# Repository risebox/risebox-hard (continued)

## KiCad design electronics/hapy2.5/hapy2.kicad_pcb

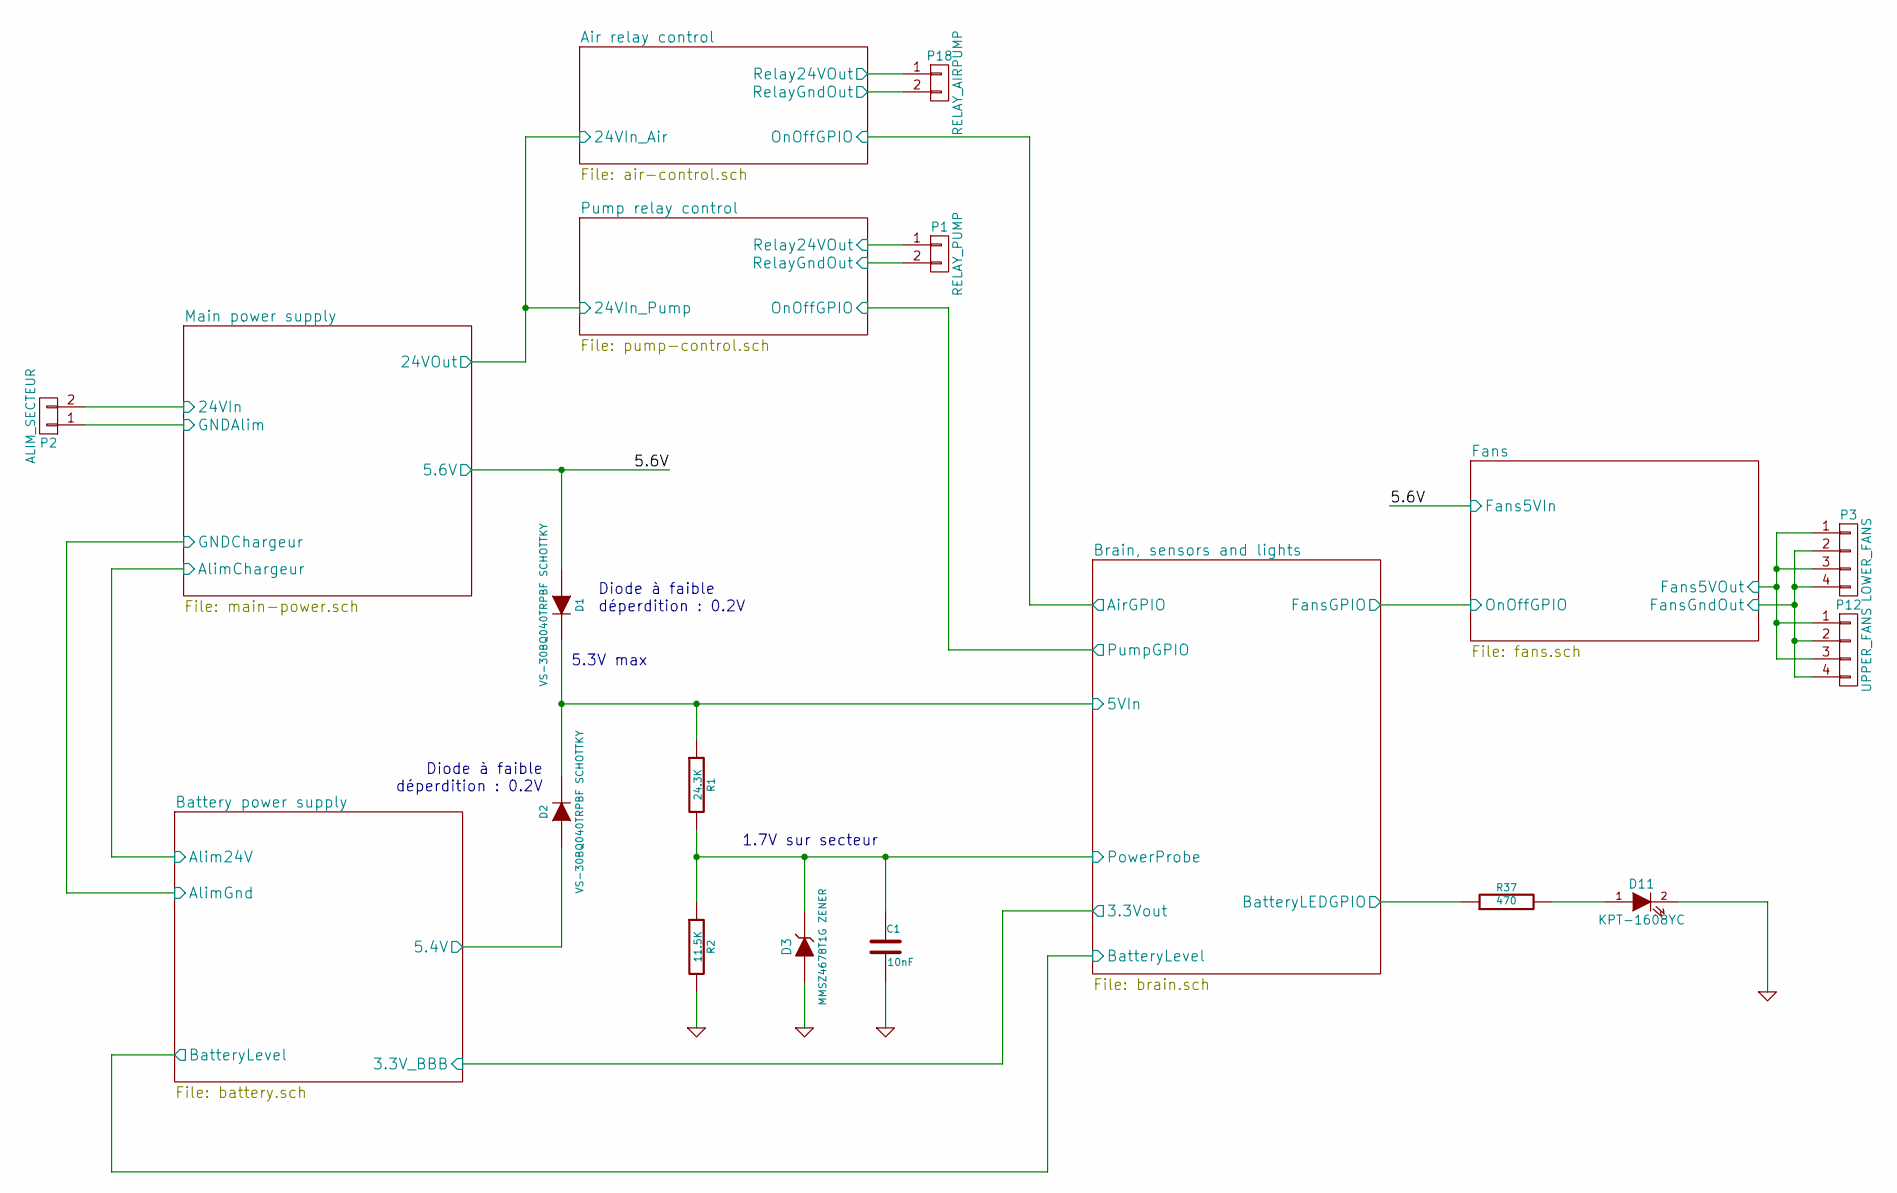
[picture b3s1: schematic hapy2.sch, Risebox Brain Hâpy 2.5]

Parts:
C1: 10nF; C_0402
D1, D2: VS-30BQ040TRPBF SCHOTTKY; DO-214AB
D3: MMSZ4678T1G ZENER; DIODE_SOD-123
D11: KPT-1608YC; LED_KPH_1608
P1: RELAY_PUMP; mpt_0,5%2f2-2,54
P2: ALIM_SECTEUR; mpt_0,5%2f2-2,54
P3: LOWER_FANS; mpt_0,5%2f4-2,54
P12: UPPER_FANS; mpt_0,5%2f4-2,54
P18: RELAY_AIRPUMP; mpt_0,5%2f2-2,54
R1: 24.3K; R_0603
R2: 11.5K; R_0603
R37: 470; R_0603

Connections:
/Air relay control/24VIn_Air: P1.1, P18.1; also elsewhere on the board
/Air relay control/RelayGndOut: P18.2; also elsewhere on the board
/Battery power supply/5.4V: D2.1 (A); also elsewhere on the board
/Brain, sensors and lights/5VIn: D1.2 (K), D2.2 (K), R1.1; also elsewhere on the board
/Brain, sensors and lights/BatteryLEDGPIO: R37.1; also elsewhere on the board
/Brain, sensors and lights/PowerProbe: C1.1, D3.2 (K), R1.2, R2.1; also elsewhere on the board
/Fans/FansGndOut: P3.2, P3.4, P12.2, P12.4; also elsewhere on the board
/Main power supply/5.6V: D1.1 (A), P3.1, P3.3, P12.1, P12.3; also elsewhere on the board
/Main power supply/24VIn: P2.2; also elsewhere on the board
/Pump relay control/RelayGndOut: P1.2; also elsewhere on the board
GND: C1.2, D3.1 (A), D11.2 (K), P2.1, R2.2; also elsewhere on the board
unnamed: D11.1 (A), R37.2

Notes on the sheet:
Diode à faible déperdition : 0.2V
5.3V max
1.7V sur secteur

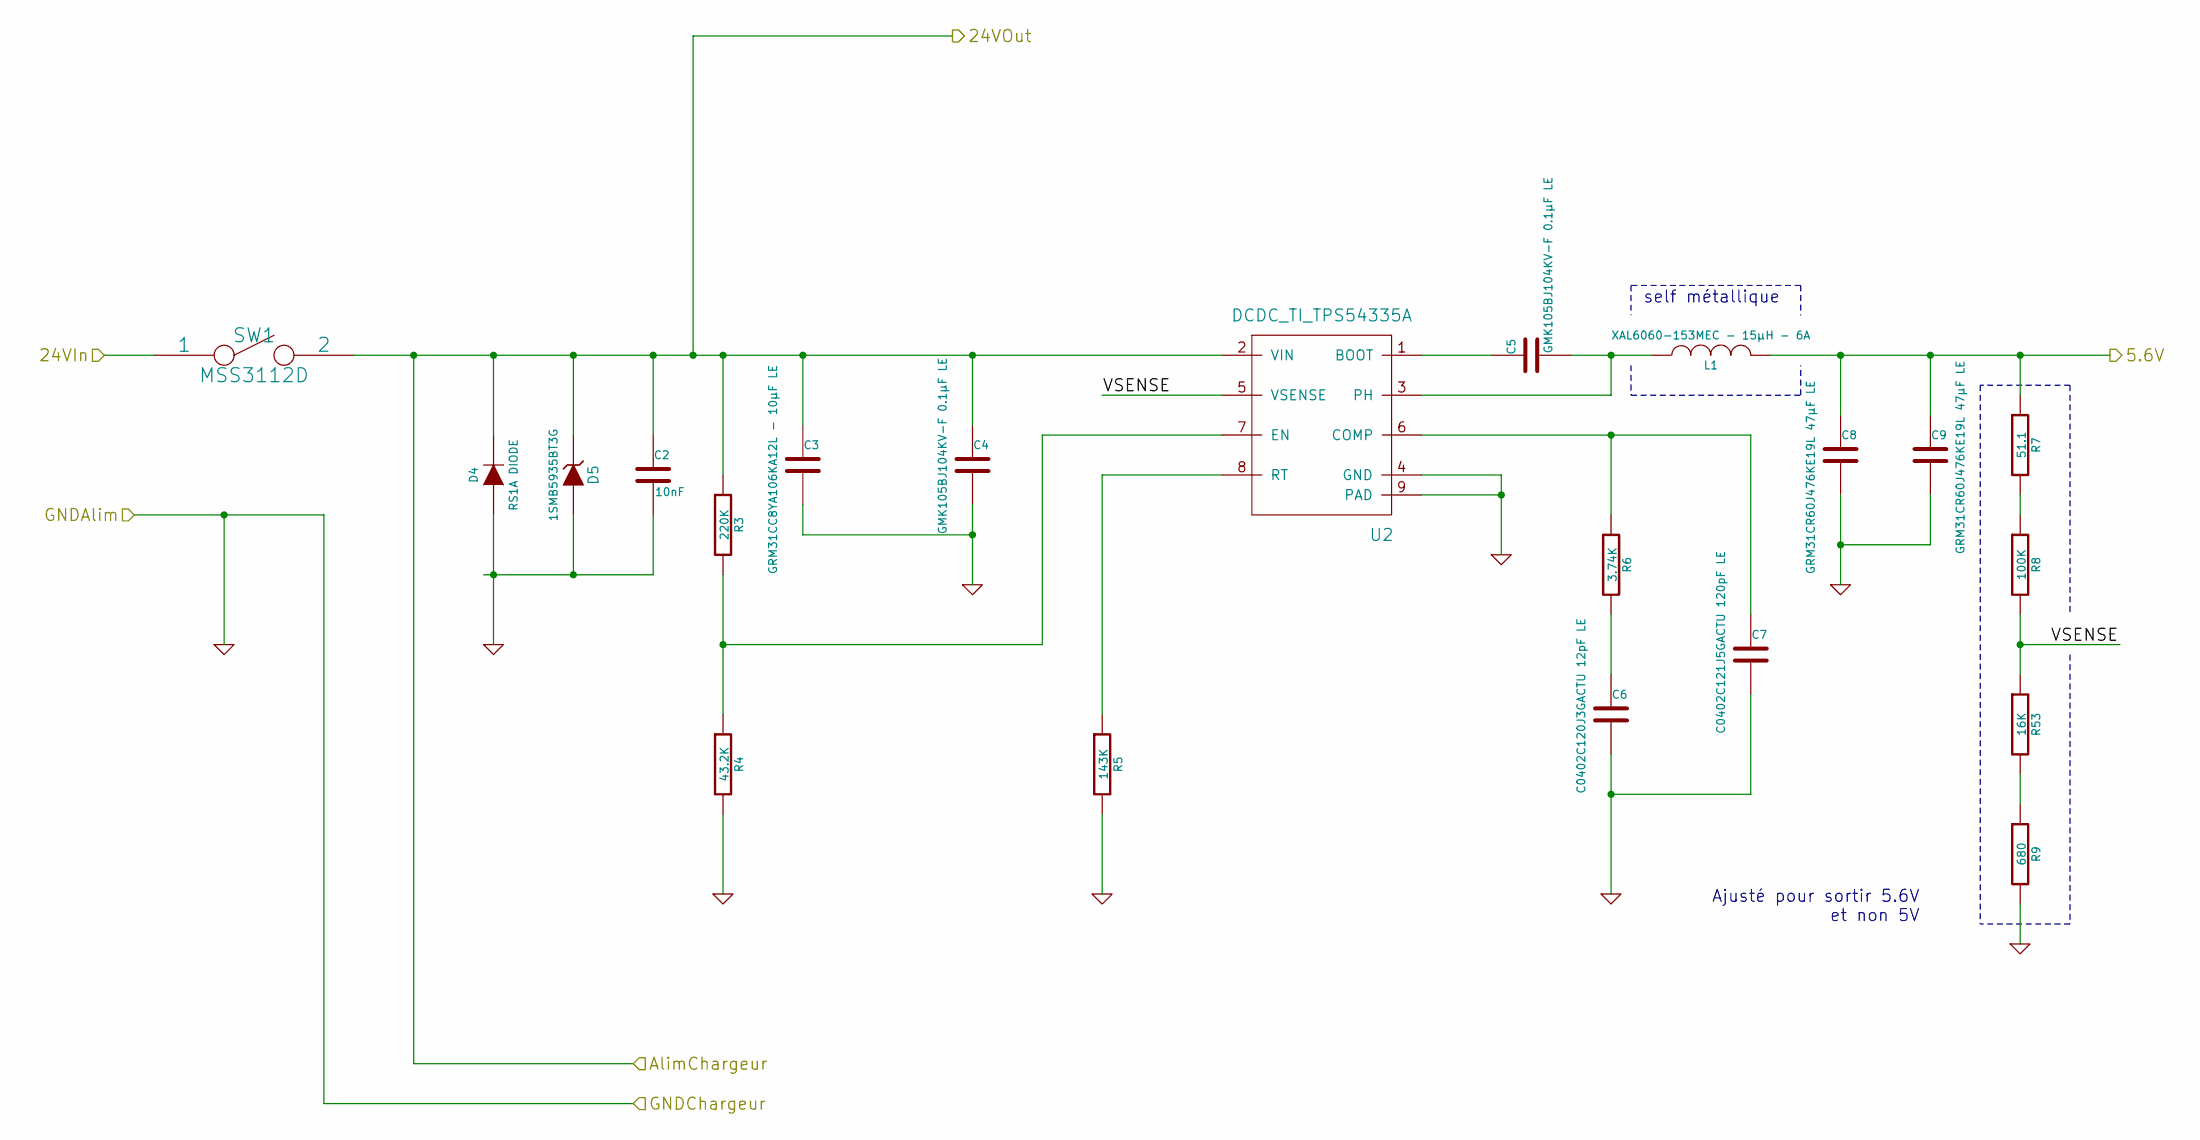
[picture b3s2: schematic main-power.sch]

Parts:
C2: 10nF; C_1206
C3: GRM31CC8YA106KA12L - 10µF LE; C_1206
C4, C5: GMK105BJ104KV-F 0.1µF LE; C_0402
C6: C0402C120J3GACTU 12pF LE; C_0402
C7: C0402C121J5GACTU 120pF LE; C_0402
C8, C9: GRM31CR60J476KE19L 47µF LE; C_1206
D4: RS1A DIODE; AB2_DO-214AC
D5: 1SMB5935BT3G; DIODE_SMB_Standard
L1: XAL6060-153MEC - 15µH - 6A; SELF_COILCRAFT_XAL6060-153
R3: 220K; R_0603
R4: 43.2K; R_0603
R5: 143K; R_0603
R6: 3.74K; R_0603
R7: 51.1; R_0603
R8: 100K; R_0603
R9: 680; R_0603
R53: 16K; R_0603
SW1: MSS3112D; SPDT_MSS3112D
U2: DCDC_TI_TPS54335A; DCDC-TPS54335A

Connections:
/Air relay control/24VIn_Air: C2.1, C3.1, C4.1, D4.2 (K), D5.2 (K), R3.1, SW1.2, U2.2 (VIN); also elsewhere on the board
/Main power supply/5.6V: C8.1, C9.1, L1.2, R7.1; also elsewhere on the board
/Main power supply/24VIn: SW1.1; also elsewhere on the board
/Main power supply/VSENSE: R8.2, R53.1, U2.5 (VSENSE)
GND: C2.2, C3.2, C4.2, C6.2, C7.2, C8.2, C9.2, D4.1 (A), D5.1 (A), R4.2, R5.2, R9.2, U2.4 (GND), U2.9 (PAD); also elsewhere on the board
unnamed: C5.1, U2.1 (BOOT)
unnamed: C5.2, L1.1, U2.3 (PH)
unnamed: C6.1, R6.2
unnamed: C7.1, R6.1, U2.6 (COMP)
unnamed: R3.2, R4.1, U2.7 (EN)
unnamed: R5.1, U2.8 (RT)
unnamed: R7.2, R8.1
unnamed: R9.1, R53.2

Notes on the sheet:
self métallique
Ajusté pour sortir 5.6V et non 5V

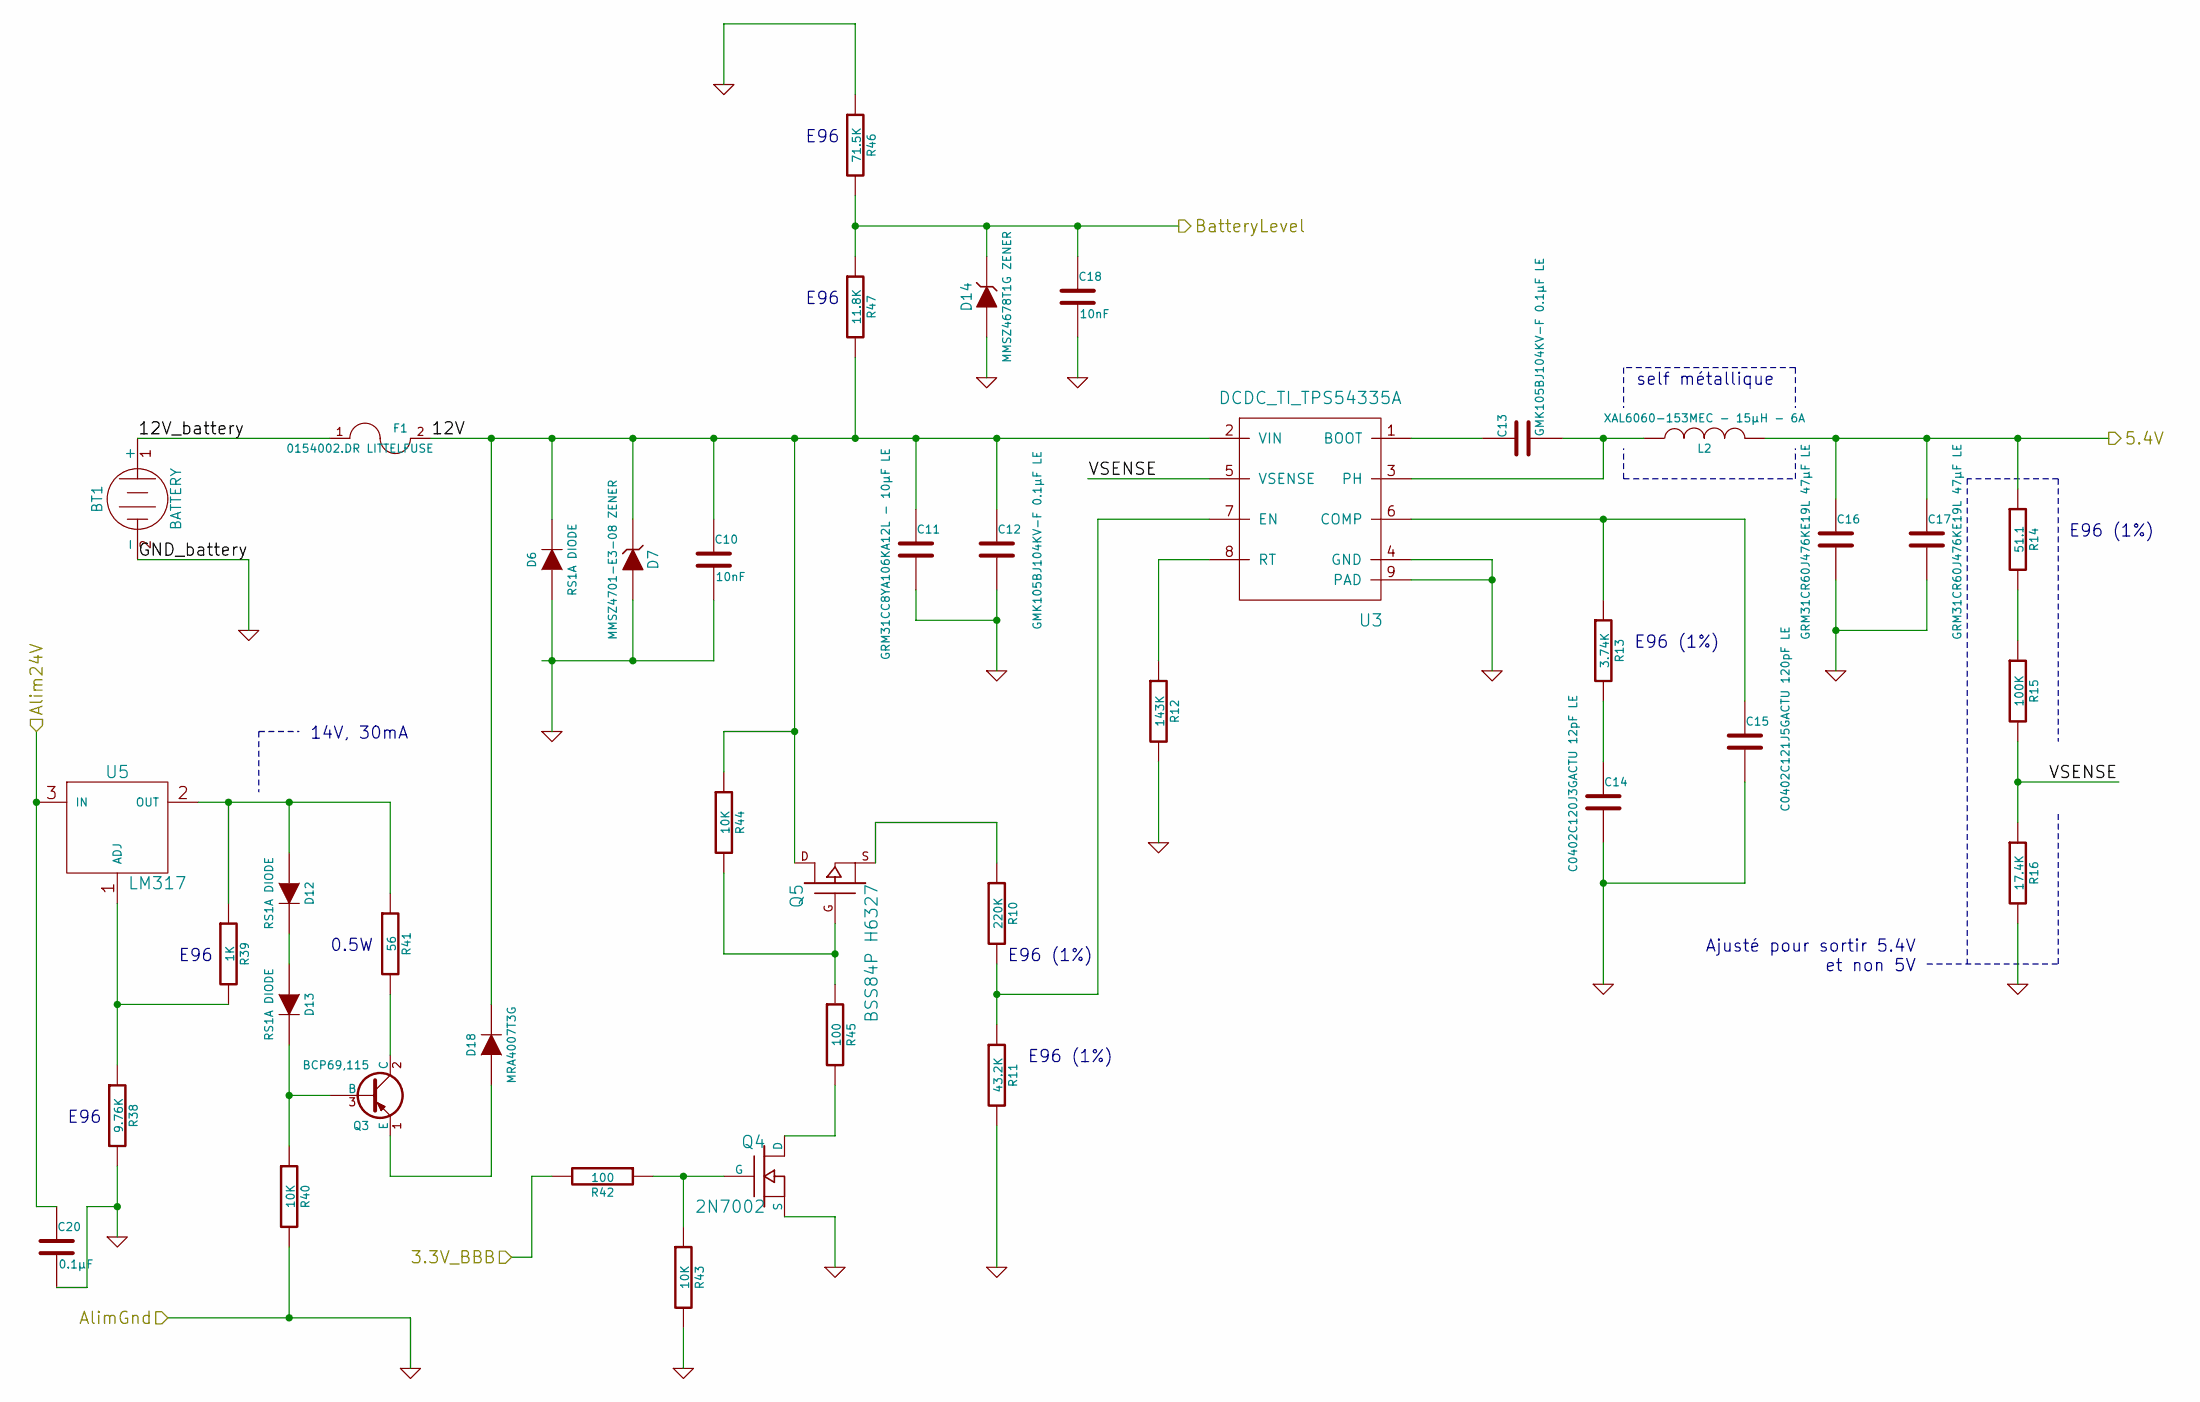
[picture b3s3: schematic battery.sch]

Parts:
BT1: BATTERY; mpt_0,5%2f2-2,54
C10: 10nF; C_1206
C11: GRM31CC8YA106KA12L - 10µF LE; C_1206
C12: GMK105BJ104KV-F 0.1µF LE; C_1206
C13: GMK105BJ104KV-F 0.1µF LE; C_0402
C14: C0402C120J3GACTU 12pF LE; C_0402
C15: C0402C121J5GACTU 120pF LE; C_0402
C16, C17: GRM31CR60J476KE19L 47µF LE; C_1206
C18: 10nF; C_0402
C20: 0.1µF
D6, D12, D13: RS1A DIODE; AB2_DO-214AC
D7: MMSZ4701-E3-08 ZENER; DIODE_SOD-123
D14: MMSZ4678T1G ZENER; DIODE_SOD-123
D18: MRA4007T3G
F1: 0154002.DR LITTELFUSE; LITTELFUSE_0154002.DR
L2: XAL6060-153MEC - 15µH - 6A; SELF_COILCRAFT_XAL6060-153
Q3: BCP69,115; SOT126_SOT32_Housing_Vertical
Q4: 2N7002; SOT-23-FET
Q5: BSS84P H6327; SOT-23-FET
R10: 220K; R_0805
R11: 43.2K; R_0603
R12: 143K; R_0603
R13: 3.74K; R_0603
R14: 51.1; R_0603
R15: 100K; R_0603
R16: 17.4K; R_0603
R38: 9.76K; R_0603
R39: 1K; R_0805
R40, R43: 10K; R_0603
R41: 56; R_1206
R42, R45: 100; R_0603
R44: 10K; R_0805
R46: 71.5K; R_0603
R47: 11.8K; R_0805
U3: DCDC_TI_TPS54335A; DCDC-TPS54335A
U5: LM317; AB2_SOT223

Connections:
/Air relay control/24VIn_Air: C20.1, U5.3 (IN); also elsewhere on the board
/Battery power supply/3.3V_BBB: R42.2; also elsewhere on the board
/Battery power supply/5.4V: C16.1, C17.1, L2.2, R14.1; also elsewhere on the board
/Battery power supply/12V: C10.1, C11.1, C12.1, D6.2 (K), D7.2 (K), D18.2 (K), F1.2, Q5.D, R44.1, R47.2, U3.2 (VIN)
/Battery power supply/12V_battery: BT1.1 (+), F1.1
/Battery power supply/BatteryLevel: C18.1, D14.2 (K), R46.2, R47.1; also elsewhere on the board
/Battery power supply/VSENSE: R15.2, R16.1, U3.5 (VSENSE)
GND: BT1.2 (-), C10.2, C11.2, C12.2, C14.2, C15.2, C16.2, C17.2, C18.2, C20.2, D6.1 (A), D7.1 (A), D14.1 (A), Q4.S, R11.2, R12.2, R16.2, R38.2, R40.2, R43.2, R46.1, U3.4 (GND), U3.9 (PAD); also elsewhere on the board
unnamed: C13.1, U3.1 (BOOT)
unnamed: C13.2, L2.1, U3.3 (PH)
unnamed: C14.1, R13.2
unnamed: C15.1, R13.1, U3.6 (COMP)
unnamed: D12.1 (A), R39.1, R41.1, U5.2 (OUT)
unnamed: D12.2 (K), D13.1 (A)
unnamed: D13.2 (K), Q3.3 (B), R40.1
unnamed: D18.1 (A), Q3.1 (E)
unnamed: Q3.2 (C), R41.2
unnamed: Q4.D, R45.2
unnamed: Q4.G, R42.1, R43.1
unnamed: Q5.G, R44.2, R45.1
unnamed: Q5.S, R10.1
unnamed: R10.2, R11.1, U3.7 (EN)
unnamed: R12.1, U3.8 (RT)
unnamed: R14.2, R15.1
unnamed: R38.1, R39.2, U5.1 (ADJ)

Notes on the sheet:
self métallique
Ajusté pour sortir 5.4V et non 5V
14V, 30mA
E96 (1%)
E96
0.5W

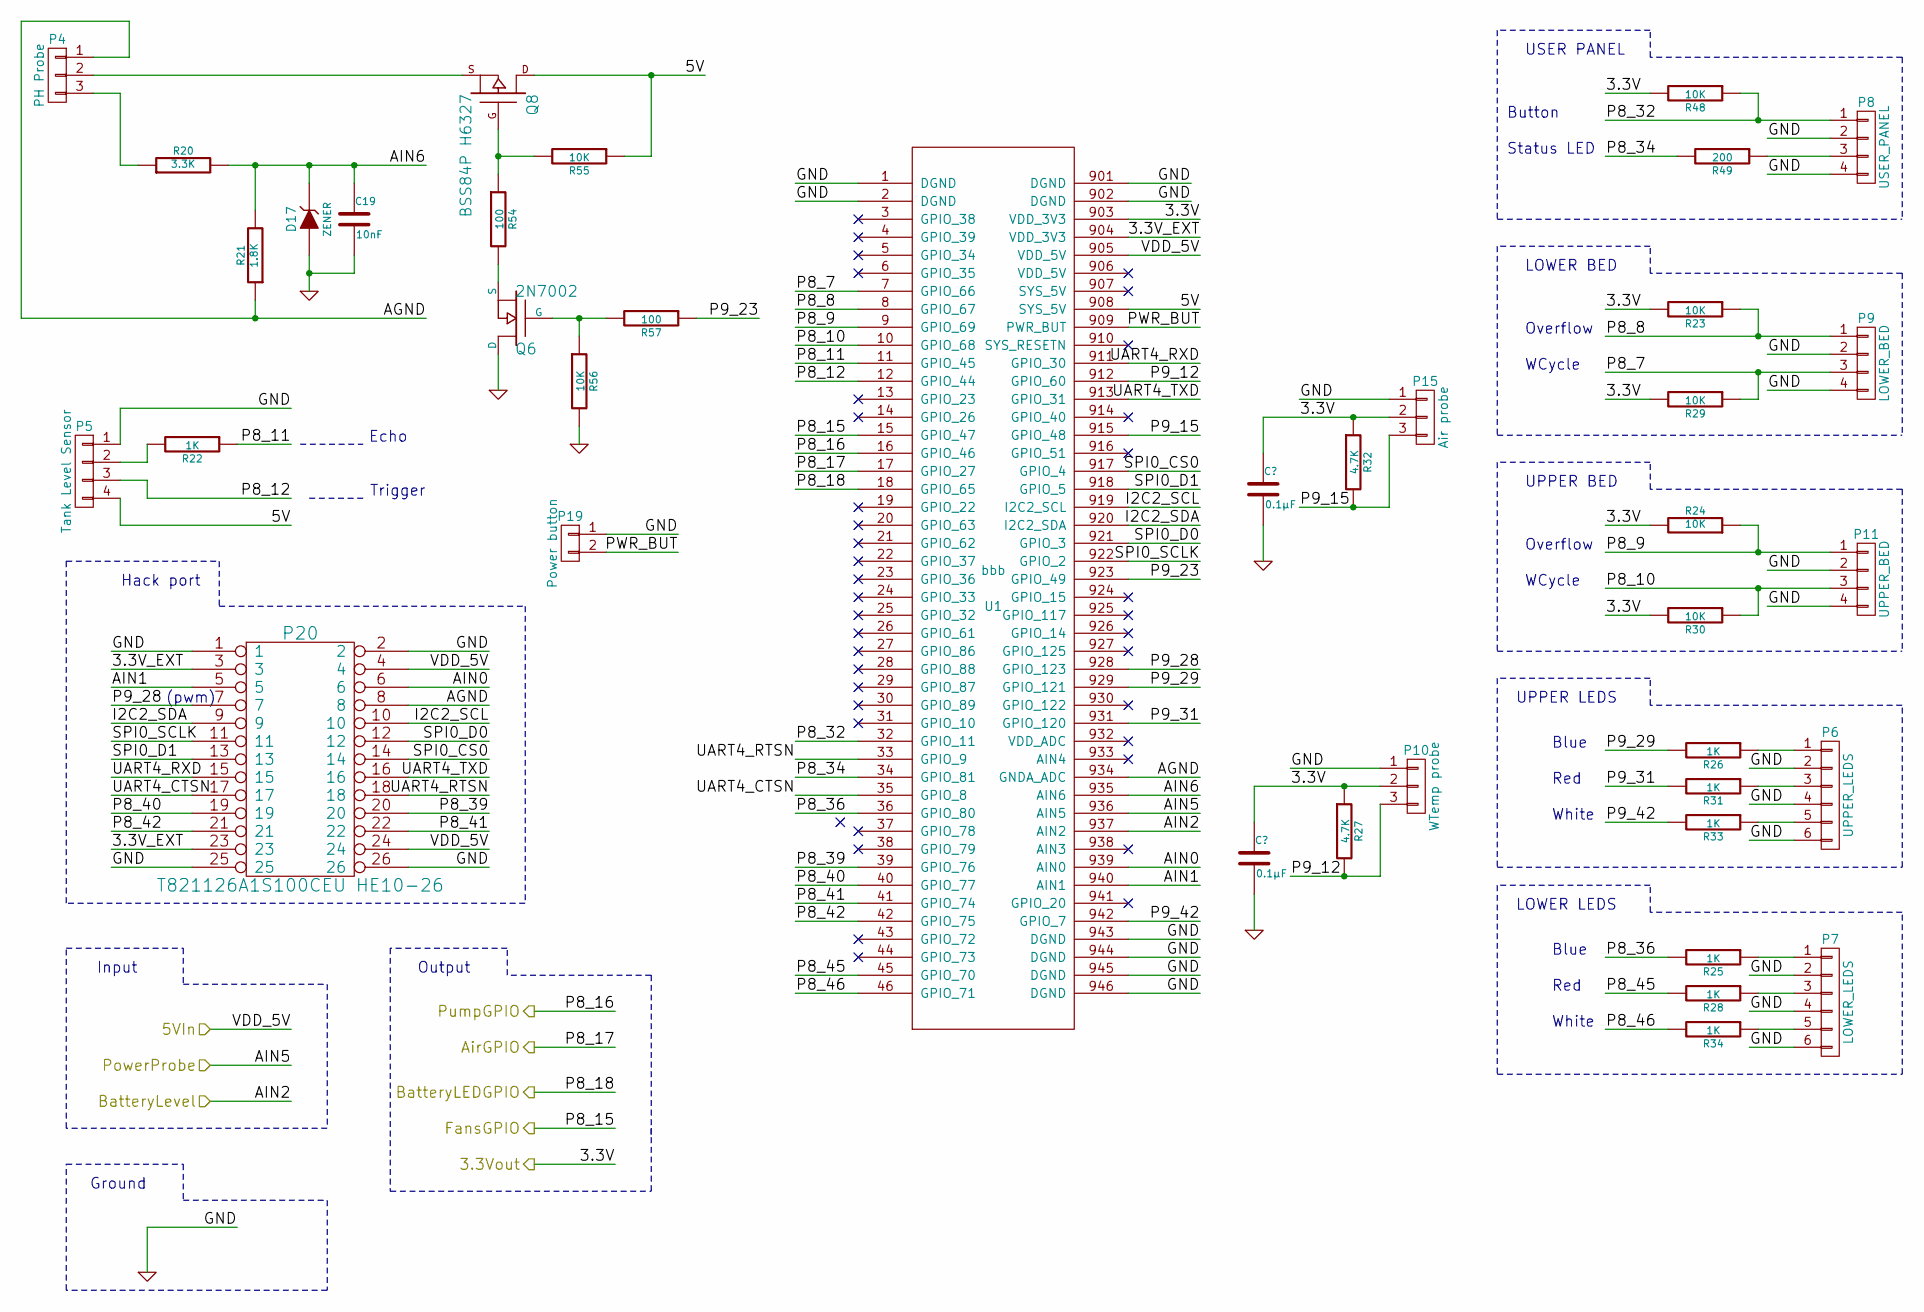
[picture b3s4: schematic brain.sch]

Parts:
C19: 10nF; C_0402
D17: ZENER; DIODE_SOD-123
P4: PH Probe; PINHEAD1-3
P5: Tank Level Sensor; mpt_0,5%2f4-2,54
P6: UPPER_LEDS; mpt_0,5%2f6-2,54
P7: LOWER_LEDS; mpt_0,5%2f6-2,54
P8: USER_PANEL; mpt_0,5%2f4-2,54
P9: LOWER_BED; mpt_0,5%2f4-2,54
P10: WTemp probe; mpt_0,5%2f3-2,54
P11: UPPER_BED; mpt_0,5%2f4-2,54
P15: Air probe; mpt_0,5%2f3-2,54
P19: Power button; mpt_0,5%2f2-2,54
P20: T821126A1S100CEU HE10-26; vasch_strip_13x2
Q6: 2N7002; SOT-23-FET
Q8: BSS84P H6327; SOT-23-FET
R20: 3.3K; R_0603
R21: 1.8K; R_0603
R22, R25, R26, R28, R31, R33, R34: 1K; R_0603
R23, R24, R29, R30, R48, R55: 10K; R_0603
R27, R32: 4.7K; R_0603
R49: 200; R_0603
R54: 100; R_0603
R56: 10K
R57: 100
U1: bbb; BBB

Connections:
/Battery power supply/3.3V_BBB: P10.2, P15.2, R23.2, R24.2, R27.1, R29.2, R30.2, R32.1, R48.2, U1.903 (VDD_3V3); also elsewhere on the board
/Battery power supply/BatteryLevel: U1.937 (AIN2); also elsewhere on the board
/Brain, sensors and lights/3.3V_EXT: P20.3, P20.23, U1.904 (VDD_3V3)
/Brain, sensors and lights/5V: P5.4, Q8.D, R55.1, U1.908 (SYS_5V)
/Brain, sensors and lights/5VIn: P20.4, P20.24, U1.905 (VDD_5V); also elsewhere on the board
/Brain, sensors and lights/AGND: P4.1, P20.8, R21.1, U1.934 (GNDA_ADC)
/Brain, sensors and lights/AIN0: P20.6, U1.939 (AIN0)
/Brain, sensors and lights/AIN1: P20.5, U1.940 (AIN1)
/Brain, sensors and lights/AIN6: C19.1, D17.2 (K), R20.2, R21.2, U1.935 (AIN6)
/Brain, sensors and lights/AirGPIO: U1.17 (GPIO_27); also elsewhere on the board
/Brain, sensors and lights/BatteryLEDGPIO: U1.18 (GPIO_65); also elsewhere on the board
/Brain, sensors and lights/FansGPIO: U1.15 (GPIO_47); also elsewhere on the board
/Brain, sensors and lights/I2C2_SCL: P20.10, U1.919 (I2C2_SCL)
/Brain, sensors and lights/I2C2_SDA: P20.9, U1.920 (I2C2_SDA)
/Brain, sensors and lights/P8_7: P9.3, R29.1, U1.7 (GPIO_66)
/Brain, sensors and lights/P8_8: P9.1, R23.1, U1.8 (GPIO_67)
/Brain, sensors and lights/P8_9: P11.1, R24.1, U1.9 (GPIO_69)
/Brain, sensors and lights/P8_10: P11.3, R30.1, U1.10 (GPIO_68)
/Brain, sensors and lights/P8_11: R22.1, U1.11 (GPIO_45)
/Brain, sensors and lights/P8_12: P5.3, U1.12 (GPIO_44)
/Brain, sensors and lights/P8_32: P8.1, R48.1, U1.32 (GPIO_11)
/Brain, sensors and lights/P8_34: R49.2, U1.34 (GPIO_81)
/Brain, sensors and lights/P8_36: R25.2, U1.36 (GPIO_80)
/Brain, sensors and lights/P8_39: P20.20, U1.39 (GPIO_76)
/Brain, sensors and lights/P8_40: P20.19, U1.40 (GPIO_77)
/Brain, sensors and lights/P8_41: P20.22, U1.41 (GPIO_74)
/Brain, sensors and lights/P8_42: P20.21, U1.42 (GPIO_75)
/Brain, sensors and lights/P8_45: R28.2, U1.45 (GPIO_70)
/Brain, sensors and lights/P8_46: R34.2, U1.46 (GPIO_71)
/Brain, sensors and lights/P9_12: P10.3, R27.2, U1.912 (GPIO_60)
/Brain, sensors and lights/P9_15: P15.3, R32.2, U1.915 (GPIO_48)
/Brain, sensors and lights/P9_23: R57.1, U1.923 (GPIO_49)
/Brain, sensors and lights/P9_28: P20.7, U1.928 (GPIO_123)
/Brain, sensors and lights/P9_29: R26.2, U1.929 (GPIO_121)
/Brain, sensors and lights/P9_31: R31.2, U1.931 (GPIO_120)
/Brain, sensors and lights/P9_42: R33.2, U1.942 (GPIO_7)
/Brain, sensors and lights/PWR_BUT: P19.2, U1.909 (PWR_BUT)
/Brain, sensors and lights/PowerProbe: U1.936 (AIN5); also elsewhere on the board
/Brain, sensors and lights/SPI0_CS0: P20.14, U1.917 (GPIO_4)
/Brain, sensors and lights/SPI0_D0: P20.12, U1.921 (GPIO_3)
/Brain, sensors and lights/SPI0_D1: P20.13, U1.918 (GPIO_5)
/Brain, sensors and lights/SPI0_SCLK: P20.11, U1.922 (GPIO_2)
/Brain, sensors and lights/UART4_CTSN: P20.17, U1.35 (GPIO_8)
/Brain, sensors and lights/UART4_RTSN: P20.18, U1.33 (GPIO_9)
/Brain, sensors and lights/UART4_RXD: P20.15, U1.911 (GPIO_30)
/Brain, sensors and lights/UART4_TXD: P20.16, U1.913 (GPIO_31)
/Pump relay control/OnOffGPIO: U1.16 (GPIO_46); also elsewhere on the board
GND: C19.2, D17.1 (A), P5.1, P6.2, P6.4, P6.6, P7.2, P7.4, P7.6, P8.2, P8.4, P9.2, P9.4, P10.1, P11.2, P11.4, P15.1, P19.1, P20.1, P20.2, P20.25, P20.26, Q6.D, R56.2, U1.1 (DGND), U1.2 (DGND), U1.901 (DGND), U1.902 (DGND), U1.943 (DGND), U1.944 (DGND), U1.945 (DGND), U1.946 (DGND); also elsewhere on the board
unnamed: P4.2, Q8.S
unnamed: P4.3, R20.1
unnamed: P5.2, R22.2
unnamed: P6.1, R26.1
unnamed: P6.3, R31.1
unnamed: P6.5, R33.1
unnamed: P7.1, R25.1
unnamed: P7.3, R28.1
unnamed: P7.5, R34.1
unnamed: P8.3, R49.1
unnamed: Q6.G, R56.1, R57.2
unnamed: Q6.S, R54.2
unnamed: Q8.G, R54.1, R55.2

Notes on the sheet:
Echo
Trigger
Input
Output
Ground
(pwm)
Hack port
Blue
Red
White
LOWER LEDS
UPPER LEDS
Overflow
WCycle
UPPER BED
LOWER BED
Button
Status LED
USER PANEL

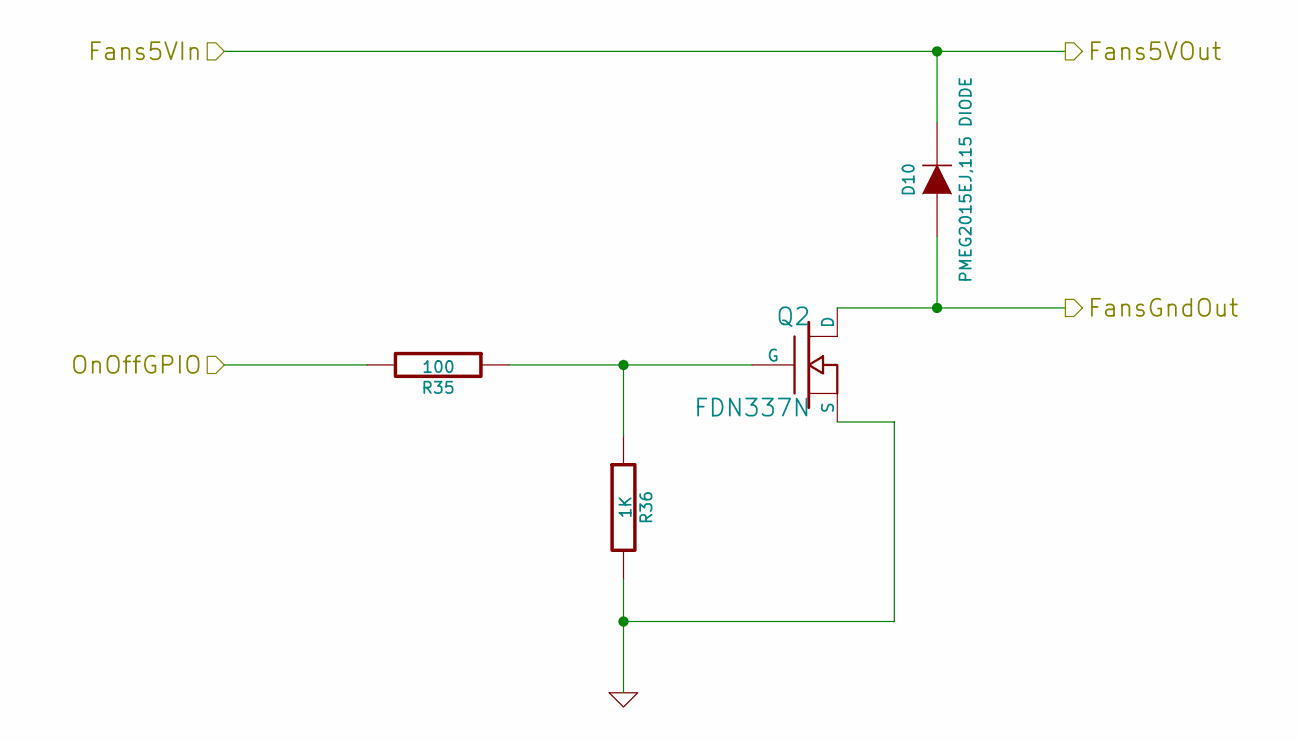
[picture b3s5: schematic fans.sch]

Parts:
D10: PMEG2015EJ,115 DIODE; DIODE_SOD-323
Q2: FDN337N; SOT-23-FET
R35: 100; R_0603
R36: 1K; R_0603

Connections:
/Brain, sensors and lights/FansGPIO: R35.2; also elsewhere on the board
/Fans/FansGndOut: D10.1 (A), Q2.D; also elsewhere on the board
/Main power supply/5.6V: D10.2 (K); also elsewhere on the board
GND: Q2.S, R36.2; also elsewhere on the board
unnamed: Q2.G, R35.1, R36.1

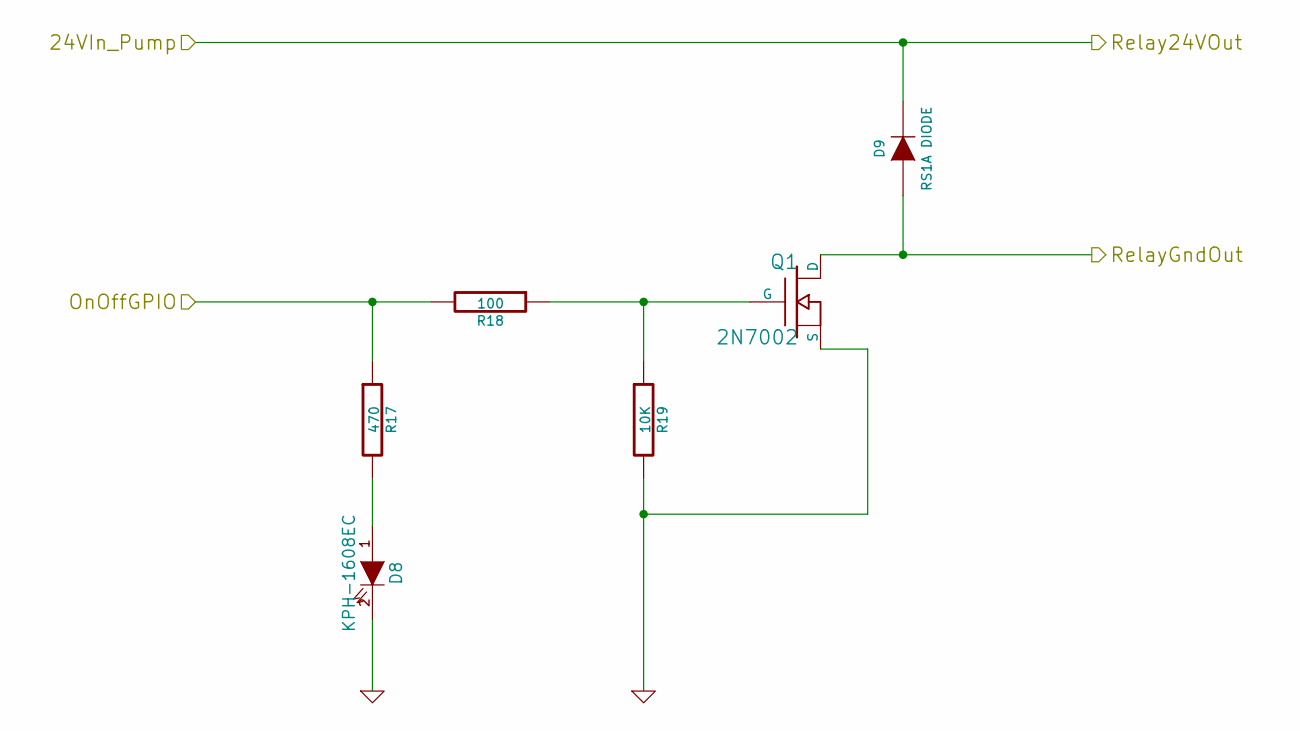
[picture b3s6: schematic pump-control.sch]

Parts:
D8: KPH-1608EC; LED_KPH_1608
D9: RS1A DIODE; AB2_DO-214AC
Q1: 2N7002; SOT-23-FET
R17: 470; R_0603
R18: 100; R_0603
R19: 10K; R_0603

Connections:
/Air relay control/24VIn_Air: D9.2 (K); also elsewhere on the board
/Pump relay control/OnOffGPIO: R17.1, R18.2; also elsewhere on the board
/Pump relay control/RelayGndOut: D9.1 (A), Q1.D; also elsewhere on the board
GND: D8.2 (K), Q1.S, R19.2; also elsewhere on the board
unnamed: D8.1 (A), R17.2
unnamed: Q1.G, R18.1, R19.1

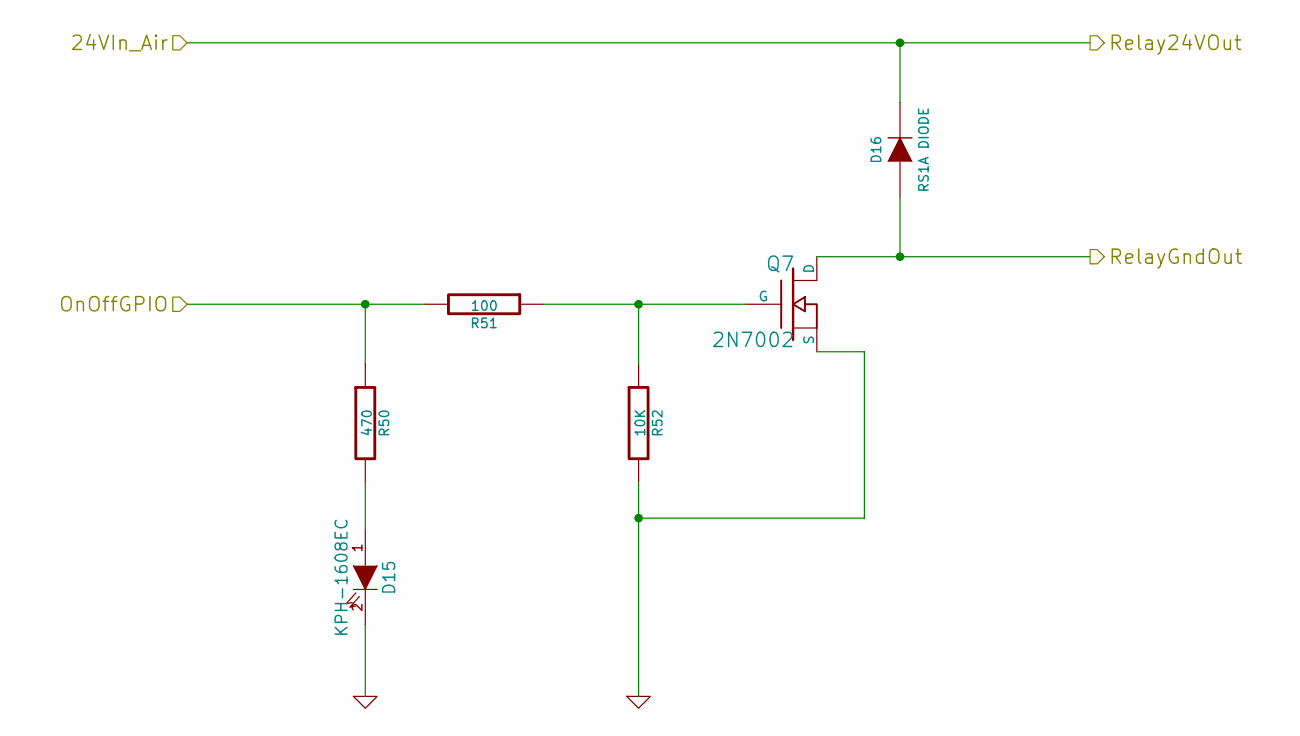
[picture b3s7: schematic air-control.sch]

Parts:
D15: KPH-1608EC; LED_KPH_1608
D16: RS1A DIODE; AB2_DO-214AC
Q7: 2N7002; SOT-23-FET
R50: 470; R_0603
R51: 100; R_0603
R52: 10K; R_0603

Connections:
/Air relay control/24VIn_Air: D16.2 (K); also elsewhere on the board
/Air relay control/RelayGndOut: D16.1 (A), Q7.D; also elsewhere on the board
/Brain, sensors and lights/AirGPIO: R50.1, R51.2; also elsewhere on the board
GND: D15.2 (K), Q7.S, R52.2; also elsewhere on the board
unnamed: D15.1 (A), R50.2
unnamed: Q7.G, R51.1, R52.1

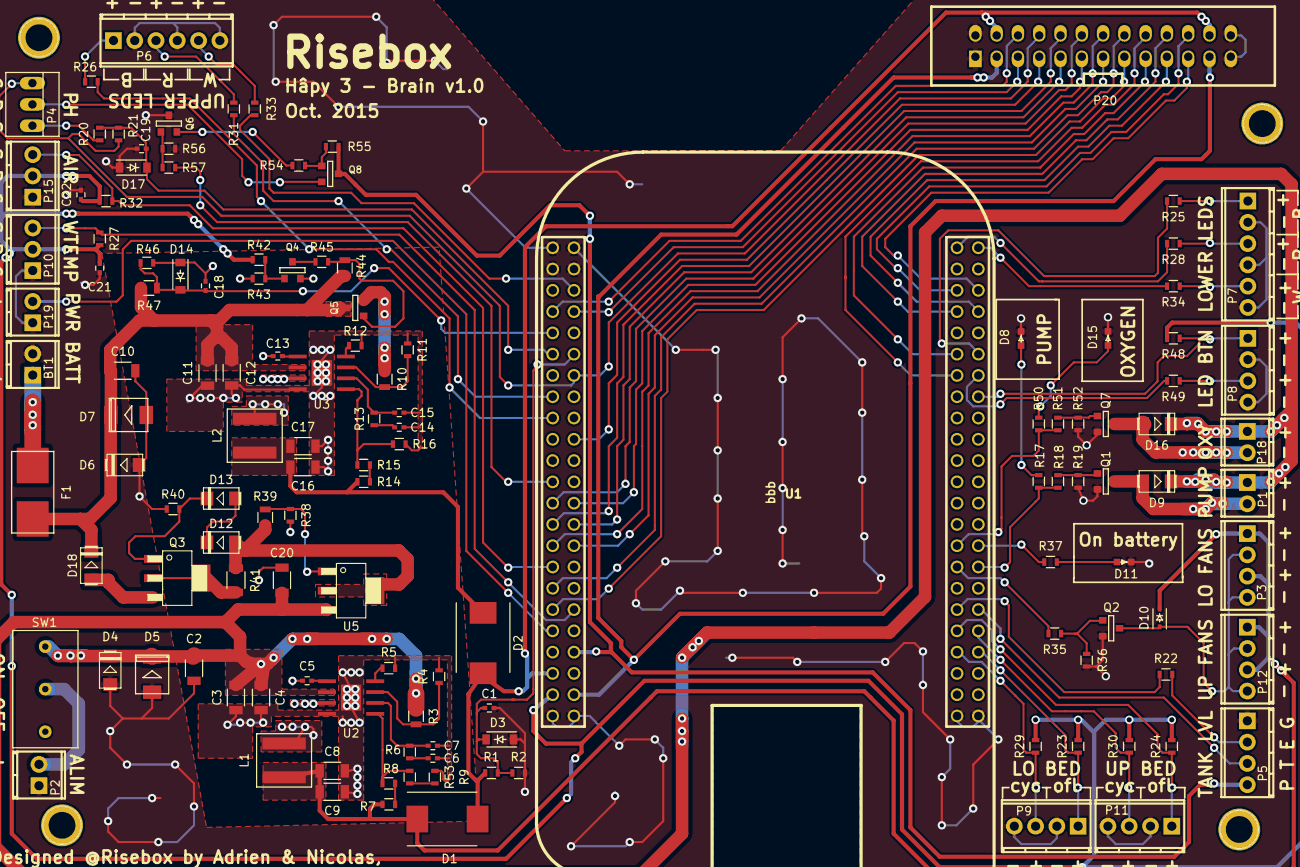
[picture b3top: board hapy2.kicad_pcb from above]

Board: 2 copper layers, 130 parts (0 on the bottom side), 103 nets.

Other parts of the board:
C21, C22: 0.1µF; C_0402

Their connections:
/Battery power supply/3.3V_BBB: C21.1, C22.1; also elsewhere on the board
GND: C21.2, C22.2; also elsewhere on the board

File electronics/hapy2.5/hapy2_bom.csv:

"Id";"Designator";"Package";"Quantity";"Designation";"Supplier and ref";
1;"C1,C18";"C_0402";2;"10nF";;;
2;"C3,C11";"C_1206";2;"GRM31CC8YA106KA12L - 10µF LE";;;
3;"C5,C13";"C_0402";2;"GMK105BJ104KV-F 0.1µF LE";;;
4;"C6,C14";"C_0402";2;"C0402C120J3GACTU 12pF LE";;;
5;"C7,C15";"C_0402";2;"C0402C121J5GACTU 120pF LE";;;
6;"C8,C9,C16,C17";"C_1206";4;"GRM31CR60J476KE19L 47µF LE";;;
7;"C12,C4";"C_1206";2;"GMK105BJ104KV-F 0.1µF LE";;;
8;"D1,D2";"DO-214AB";2;"VS-30BQ040TRPBF SCHOTTKY";;;
9;"D3";"DIODE_SOD-123";1;"MMSZ4678T1G ZENER";;;
10;"D4,D6,D9,D12,D13,D16";"AB2_DO-214AC";6;"RS1A DIODE";;;
11;"D5";"DIODE_SMB_Standard";1;"1SMB5935BT3G";;;
12;"D7";"DIODE_SOD-123";1;"MMSZ4701-E3-08 ZENER";;;
13;"D8,D15";"LED_KPH_1608";2;"KPH-1608EC";;;
14;"D10";"DIODE_SOD-323";1;"PMEG2015EJ,115 DIODE";;;
15;"D11";"LED_KPH_1608";1;"KPT-1608YC";;;
16;"D14";"DIODE_SOD-123";1;"MMSZ4678T1G  ZENER";;;
17;"F1";"LITTELFUSE_0154002.DR";1;"0154002.DR  LITTELFUSE";;;
18;"L1,L2";"SELF_COILCRAFT_XAL6060-153";2;"XAL6060-153MEC - 15µH - 6A";;;
19;"P4";"PINHEAD1-3";1;"PH Probe";;;
20;"Q1,Q2,Q4,Q6,Q7";"SOT-23-FET";5;"2N7002";;;
21;"Q3";"SOT126_SOT32_Housing_Vertical";1;"BD140";;;
22;"Q5";"SOT-23-FET";1;"BSS84P H6327";;;
23;"R1";"R_0603";1;"24.3K";;;
24;"R2";"R_0603";1;"11.5K";;;
25;"R4,R11";"R_0603";2;"43.2K";;;
26;"R5,R12";"R_0603";2;"143K";;;
27;"R6,R13";"R_0603";2;"3.74K";;;
28;"R7,R14";"R_0603";2;"51.1";;;
29;"R8,R15";"R_0603";2;"100K";;;
30;"R9";"R_0603";1;"680";;;
31;"R16";"R_0603";1;"17.4K";;;
32;"R17,R37,R50";"R_0603";3;"470";;;
33;"R18,R35,R42,R45,R51";"R_0603";5;"100";;;
34;"R19,R22,R25,R26,R28,R31,R33,R34,R36,R52";"R_0603";10;"1K";;;
35;"R20";"R_0603";1;"3.3K";;;
36;"R21";"R_0603";1;"1.8K";;;
37;"R23,R24,R29,R30,R40,R43,R48";"R_0603";7;"10K";;;
38;"R27,R32";"R_0603";2;"4.7K";;;
39;"R38";"R_0603";1;"36K";;;
40;"R46";"R_0603";1;"71.5K";;;
41;"R49";"R_0603";1;"200";;;
42;"R53";"R_0603";1;"16K";;;
43;"SW1";"SPDT_MSS3112D";1;"MSS3112D";;;
44;"U1";"BBB";1;"bbb";;;
45;"U5";"AB2_SOT223";1;"LM317";;;
46;"BT1";"mpt_0,5%2f2-2,54";1;"BATTERY";;;
47;"P1";"mpt_0,5%2f2-2,54";1;"RELAY_PUMP";;;
48;"P2";"mpt_0,5%2f2-2,54";1;"ALIM_SECTEUR";;;
49;"P3";"mpt_0,5%2f4-2,54";1;"LOWER_FANS";;;
50;"P5";"mpt_0,5%2f4-2,54";1;"Tank Level Sensor";;;
51;"P6";"mpt_0,5%2f6-2,54";1;"UPPER_LEDS";;;
52;"P7";"mpt_0,5%2f6-2,54";1;"LOWER_LEDS";;;
53;"P8";"mpt_0,5%2f4-2,54";1;"USER_PANEL";;;
54;"P9";"mpt_0,5%2f4-2,54";1;"LOWER_BED";;;
55;"P10";"mpt_0,5%2f3-2,54";1;"WTemp probe";;;
56;"P11";"mpt_0,5%2f4-2,54";1;"UPPER_BED";;;
57;"P12";"mpt_0,5%2f4-2,54";1;"UPPER_FANS";;;
58;"P15";"mpt_0,5%2f3-2,54";1;"Air probe";;;
59;"P18";"mpt_0,5%2f2-2,54";1;"RELAY_AIRPUMP";;;
60;"P19";"mpt_0,5%2f2-2,54";1;"Power button";;;
61;"C2,C10";"C_1206";2;"10nF";;;
62;"U2,U3";"DCDC-TPS54335A";2;"DCDC_TI_TPS54335A";;;
63;"R3,R10";"R_0805";2;"220K";;;
64;"P20";"vasch_strip_13x2";1;"HE10-26";;;
65;"R47";"R_0805";1;"11.8K";;;
66;"REF**,REF**,REF**,REF**";"1pin";4;"1pin";;;
67;"R41";"R_0805";1;"56";;;
68;"R44";"R_0805";1;"10K";;;
69;"R39";"R_0805";1;"5K";;;
